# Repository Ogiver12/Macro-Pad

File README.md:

# Macro Pad

### This repo contains the files to create a 3x3 macro pad
## Why
**Why you need a macro pad**
- It makes you faster at using your pc
- You can use it for hotkeys that you dont have space for on your normal keyboard
- It can automate lots of things

<br>**Why would I make one instead of buying**
- Its cheaper
- Its funner
- Its pretty cool

## Buy List
| **Item**                 | **Price**  |
| ------------------------ | ---------- |
| [Switches](https://mechboards.co.uk/collections/switches/products/gateron-g-pro-3-0-yellow?_pos=16&_fid=a9b4c57e8&_ss=c)                | £2.75      |
| [KB2040](https://thepihut.com/products/adafruit-kb2040-rp2040-kee-boar-driver) | £8.90      |
| [Keycaps](https://thepihut.com/products/black-dsa-keycaps-for-mx-compatible-switches-10-pack)          | £5.90      |
Shipping Switches UK | £1.80
Shipping for KB2040 + Keycaps UK | £3.90
| **Total**                | **£22.44** |

As I live in England I have cheaper shipping so the total may vary for you  <br>
This doesnt include PCB or case because I did those my self <br>
The PCB might be a bit weird because my PCB machine has limits

## Instructions

We will be using circuit python <br>
To install follow [this](https://learn.adafruit.com/adafruit-kb2040/circuitpython) guide and the download link is [here](https://circuitpython.org/board/adafruit_kb2040/)

## Images

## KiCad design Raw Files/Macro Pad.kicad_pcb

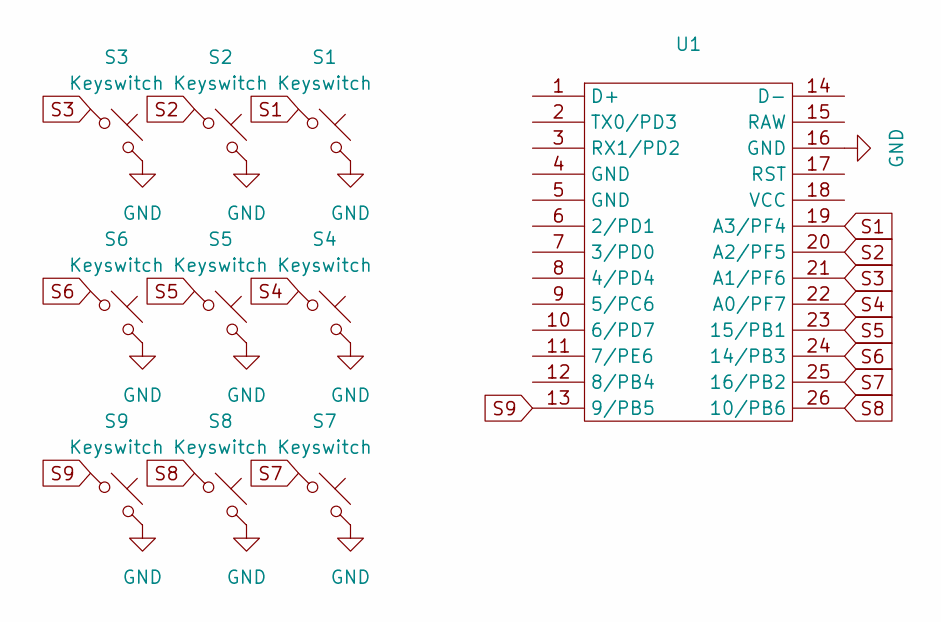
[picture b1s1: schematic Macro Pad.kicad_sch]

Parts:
S1, S2, S3, S4, S5, S6, S7, S8, S9: Keyswitch; MX_PCB_1.00u
U1: Adafruit_KB2040

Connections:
GND: S1.2, S2.2, S3.2, S4.2, S5.2, S6.2, S7.2, S8.2, S9.2, U1.16 (GND)
S1: S1.1, U1.19 (A3/PF4)
S2: S2.1, U1.20 (A2/PF5)
S3: S3.1, U1.21 (A1/PF6)
S4: S4.1, U1.22 (A0/PF7)
S5: S5.1, U1.23 (15/PB1)
S6: S6.1, U1.24 (14/PB3)
S7: S7.1, U1.25 (16/PB2)
S8: S8.1, U1.26 (10/PB6)
S9: S9.1, U1.13 (9/PB5)

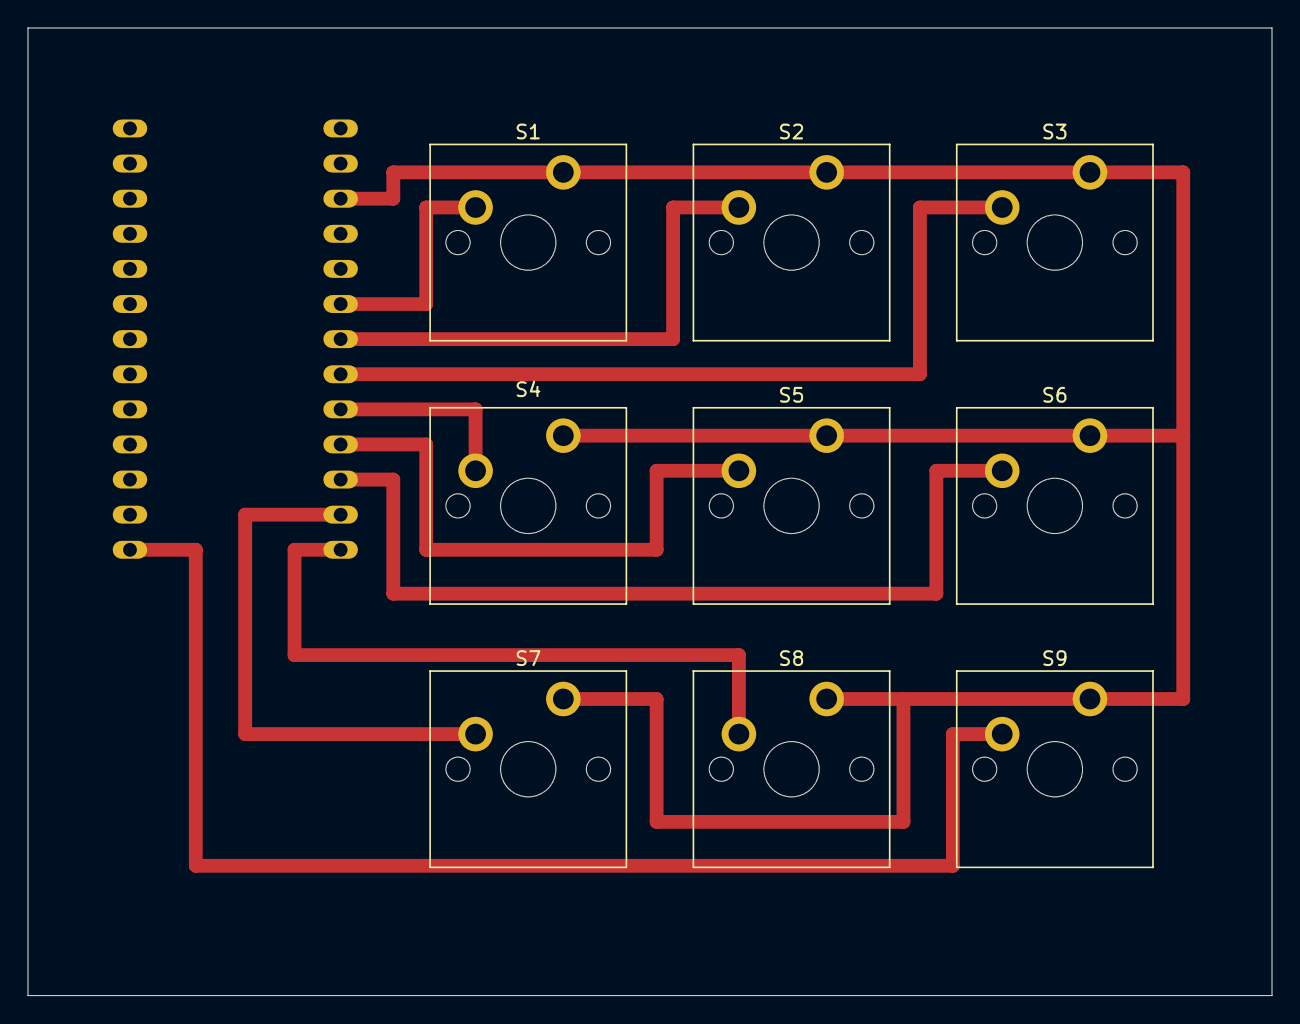
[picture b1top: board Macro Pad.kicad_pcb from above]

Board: 2 copper layers, 90.0 x 70.0 mm, 10 parts (0 on the bottom side), 10 nets.
